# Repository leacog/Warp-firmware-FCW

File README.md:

# LitShow Shield
Mikael Cognell - __mec77__ 

4B25: Coursework Item 5 

St Catharine's College 

_Demo video showing the lightshow in action, notice how the different colours respond to different sounds in the music and not simply volume (this is clearest with the second example)_

## System Overview
The LitShow shield runs on a Freescale/NXP FRDM KL03 evaluation board and  creates a real-time light show to music. The board uses a microphone to measure audio, analyses the signal on the MCU and outputs three channels of Pulse-Width Modulated 12V for LED strips. In the current firmware, the channels each respond to a different frequency band.

## LitShow Shield

#### Microphone
The shield provides two connectors for microphones and expects a 0-3.3V(max) pre-amplied signal with a DC offset at 1/2 VCC (DC offset is adjustable in software). The 3-pin connector matches the pinout of many commonly available electret microphone breakout boards - such as the [adafruit MAX4477](https://www.adafruit.com/product/1063). The 5-pin connector matches the pinout of the adafruit breakoutboard for the [MAX9814](https://www.adafruit.com/product/1713) with Automatic Gain Control.

The output from the microphone is interfaced to the MCU via a RC low-pass filter, with a -3dB frequncy of 20kHz. Furhter work on filtering could be useful, as the microphone still picks up some noise from the serial communication.
#### 12V Output Stage
Three NPN bipolar transistors ([BCP56T1G](https://www.onsemi.com/pdf/datasheet/bcp56t1-d.pdf)) in a common emitter configuration amplify the MCU PWM output. The 12V rail for the LEDs is supplied by an external power supply, connected via a barrel jack at the edge of the shield. MOSFETs would be better suited for this switching application - most enchancment mode NPN mosfets with the required current rating would make good replacements - but these were the only components I had on hand.

#### Hardware files
KiCad PCB project files are included in the repo. Note that they are designed for a single sided board, as I'm etching my PCB at home using a positive photoresist method. If ordering boards from a fab, it's worth considering rerouting the board to be double sided as certain headers (e.g. microphone header) currently have to be soldered on the wrong side and jumper resistors could be replaced by vias.

<p align="center">

</p>

## FRDM-KL03Z Firmware
The shield connects to a Freescale/NXP FRDM KL03 evaluation board, which performs the signal processing of the audio and PWM generation. The software is based on the Warp-firmware, but most of the facilities have been removed and only the serial communication, clock & power management remain. 

The software is split into three components/source files:
#### [ADC.c](src\boot\ksdk1.1.0\ADC.c) - Analog to digtal conversion
The ADC is configured to sample the audio at 38kHz to fulfill the nyquist sampling criteria for the audible range. 
To ensure a constant delay between samples, the ADC operates in continuous conversion mode. 
At the completion of a conversion (i.e. a measurment), an interupt signal is generated and the <code>ADC0_IRQHandler()</code> ISR stores the latest sample in a buffer. 

Using interupts as opposed to e.g. a polling approach allows the main FFT algorithm to run while the next batch of samples are collected.
Also, instead of checking if the buffer is filled inside the interupt routine, the ADC is deactivated (by disconnecting it from its clock source) until the buffer is transfered into the FFT buffer.
This avoids interrupts firing when the buffer is already filled and we are waiting for the previous FFT to finish.

#### [FFT.c](src\boot\ksdk1.1.0\FFT.c) - Fast Fourier Transform
To extract frequency information, a discrete fourier transform is computed on the sample buffer using a costum implementation of a recursive Radix-2 FFT algorithm. The MKL03Z32VFK4 MCU is relatively constrained in memory, with only 2KB of SRAM. To minimize memory usage and increase performance the following design choices were made.

* **The FFT algorithm is implemented in-place** i.e. operates directly on the input array. This means the memory requirements scale as $O(n)$ as opposed to $O(n log(n) )$.

* **The [twiddle factors](https://en.wikipedia.org/wiki/Twiddle\_factor) are precomputed**. This avoids any computation of trigonometric quantities at run-time. Similarly (although much less critical), the bit reversal is also implemented using a look-up table instead of by bit operations. To generate the twiddle factors and bitReverse arrays, the python command line scripts <code> [twiddle_FPA.py](src\boot\ksdk1.1.0\FFT.c)</code> and <code> [bitReverse.py](src\boot\ksdk1.1.0\FFT.c)</code> are provided under <code>/pythonScripts</code>.

* **Divides and multiplications are implemented as shifts**.  As the MCU lacks a Floating Point Unit, the twiddle factors which lie between 1 and -1 are implemented using Fixed Point Arithmetic. A twiddle factor of 1 is represented by 32768 in the FPA arithmatic. After multiplying by the twiddle factors, the result needs to be normalized down again to prevent overflows. This is why 1 is mapped to a power of 2, so that the normalization can be achived by shifting rather than by division. From practical tests, a divide by e.g. 1000 on an <code>int32_t</code> is about 30 times slower than a right shift operation. After many trials using <code>memcpy()</code> to implement fast divisions of signed integers, I found out that the compiler automatically recognizes division by powers of two and implements them as shifts -even with signed numbers where the signbit needs to be considered.

* **Bit Reversal and FFT buffers never co-exist on the stack**. To minimize the peak demand on the stack, the sample re-ordering via bit-reversal which is required at the start of the FFT is executed before the complex array is placed on the stack. This way the two arrays never co-exist on the stack. The maximum demand comes from the complex array, which is $N \times 2 \times$ <code>sizeof(int16_t)</code> of memory on the stack (514 Bytes for 128 point FFT). Still, to accomodate the high memory demand, the default Warp linker script is modified to increase maximum size of the stack, and several modifications to the Warp firmware minimize the RAM usage (which leaves more space for the stack).

The FFT.c file also provides the helper routine <code>octaves()</code> for computing the power spectrum of the FFT and splitting it into octaves. An octave bin covers twice the width in frequency of the one below one - e.g. the 2 lowest FFT bins go in the lowest octave, the 4 next bins in the second octave, the 8 next go in the third octave etc. This is better aligned with the human logarithmic perception of frequency. These octaves are used by the PWM routines to determine brightness values.

#### [PWM.c](src\boot\ksdk1.1.0\PWM.c) - Mapping frequency information to duty cycles
The PWM.c functionality sets up the Timer modules of the MCU to output PWM signals on <code>PTA5</code>, <code>PTA6</code> and <code>PTB6</code>. It contains a function to update the duty cycles for each of the channels, which accepts as arguments a <code>pwmColour</code>struct which maps the respective colour to the corresponding timer instances and channels.

Each time an FFT completes in the main loop, the power spectrum is divided into three bins using the octaves function. The value of each bin then sets the duty cycle of a corresponding colour of LED. This means one LED channel responds to base tones, one to mid-range and one to trebble. There is a lot of scope for increasing the sophistication of the mapping from DFT to brightness values, as the current firmware basically only implements a low-pass, band-pass and high-pass filter (which could be done with 4 capacitors and 4 resistors...).

It also contains some functions to perform further processing of the frequency signals. For the base note, a first-order lag is applied to make the brightness linger more, as this produces a nice effect. 

#### printFFT - rudamentary spectrum analyzer ####
In [boot.c](src\boot\ksdk1.1.0\boot.c), the printFFT function can be uncommented to display power spectrum on a serial terminal connected to the FRDM-KL03Z. This works as a rudamentary spectrum analyzer, to partly validate the functioning of the FFT but also to characterize the response of the microphone of a reference sound source is available.

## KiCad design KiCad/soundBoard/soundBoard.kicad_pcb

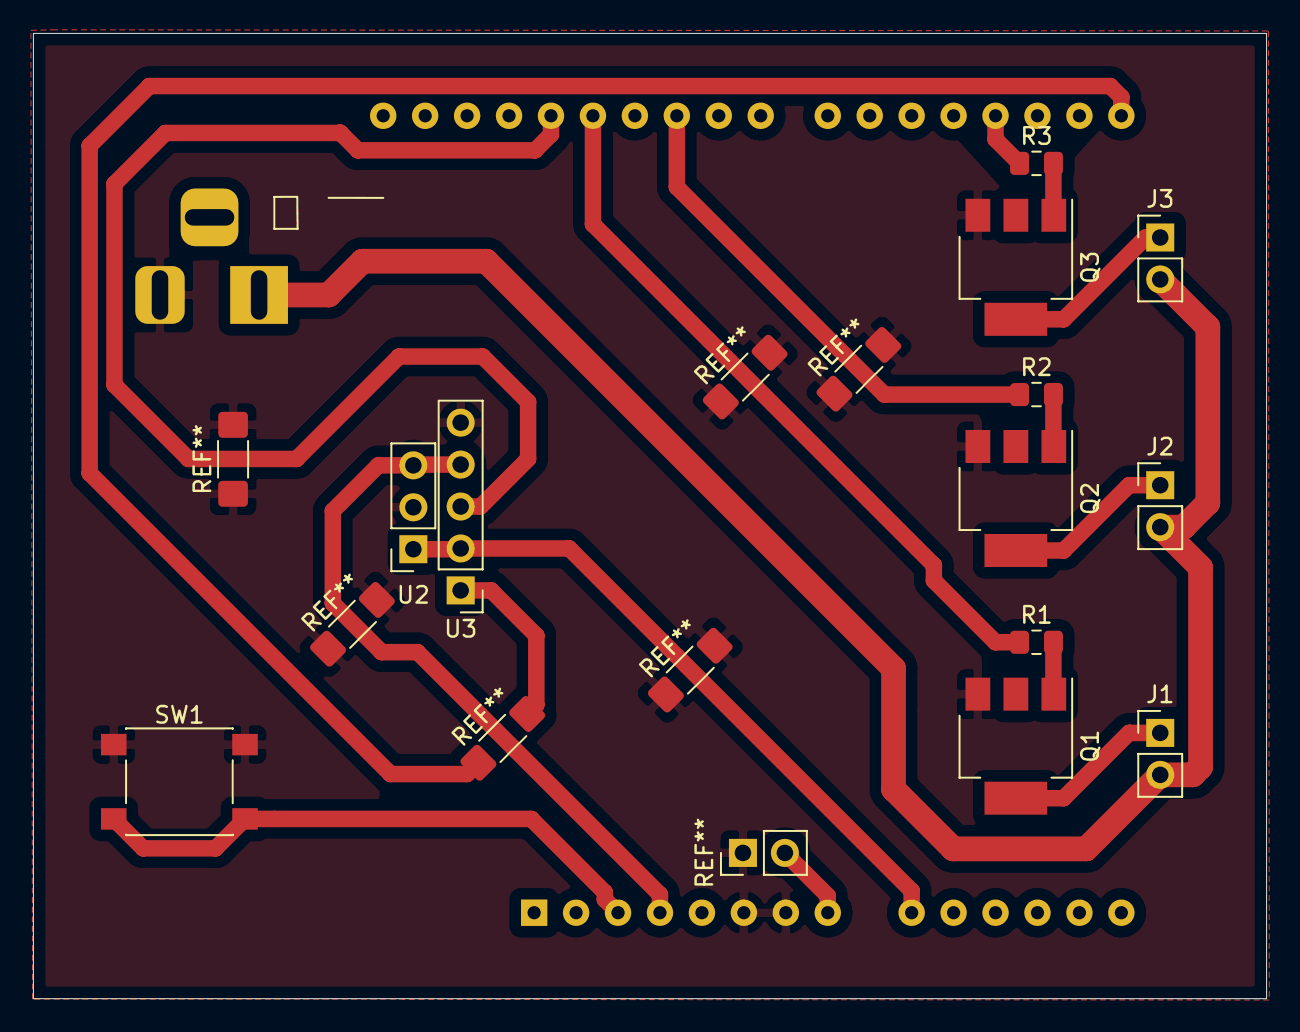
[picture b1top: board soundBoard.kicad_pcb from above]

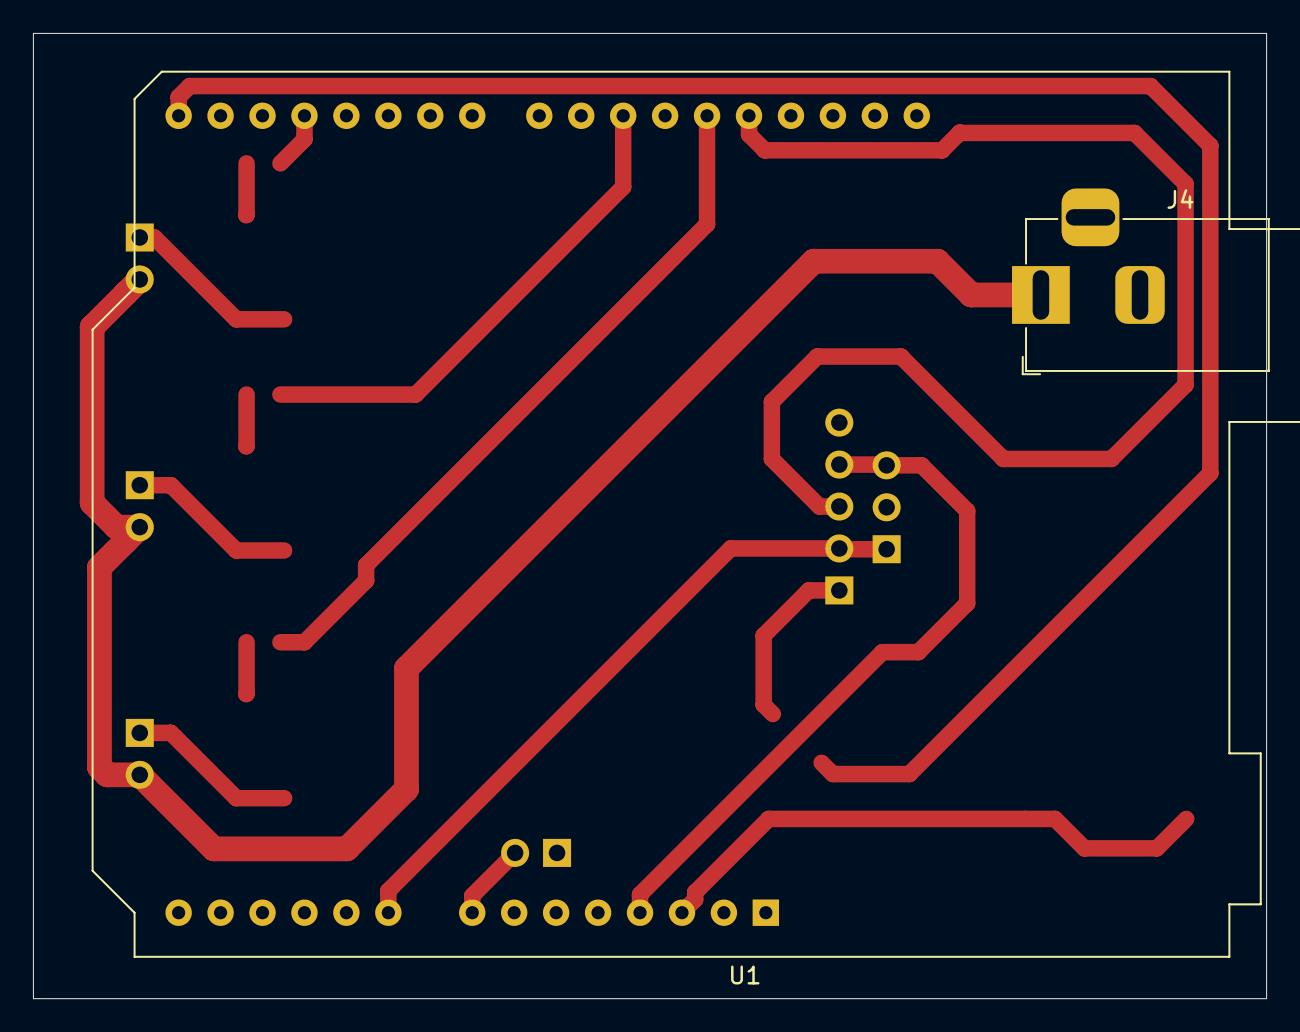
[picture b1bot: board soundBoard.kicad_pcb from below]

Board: 2 copper layers, 74.7 x 58.5 mm, 14 parts (2 on the bottom side), 16 nets.

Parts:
J1: RED; PinHeader_1x02_P2.54mm_Vertical
J2: BLUE; PinHeader_1x02_P2.54mm_Vertical
J3: GREEN; PinHeader_1x02_P2.54mm_Vertical
J4: 12_Barrel_Jack; BarrelJack_Horizontal
Q1, Q2, Q3: BCP56; SOT-223-3_TabPin2
R1, R2, R3: 670; R_0805_2012Metric_Pad1.15x1.40mm_HandSolder
SW1: SW_Push; SW_Push_1P1T_NO_6x6mm_H9.5mm
U1: FRDM-KL03Z; Arduino_UNO_R3
U2: AG_ElectretMic; PinSocket_1x03_P2.54mm_Vertical
U3: RealAG_ElectretMic; PinHeader_1x05_P2.54mm_Vertical

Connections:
+12V: J1.2, J2.2, J3.2, J4.1
/ADC_IN: U1.9, U2.1, U3.2
/AR_ADJUST: U1.15, U3.1
/BLUE_PWM: R3.1, U1.18
/GREEN_PWM: R2.1, U1.25
/RED_PWM: R1.1, U1.27
GND: J4.2, Q1.3, Q2.3, Q3.3, SW1.1, U1.6, U1.7, U1.29, U2.2, U3.5
unnamed: J1.1, Q1.2
unnamed: J2.1, Q2.2
unnamed: J3.1, Q3.2
unnamed: Q1.1, R1.2
unnamed: Q2.1, R2.2
unnamed: Q3.1, R3.2
unnamed: SW1.2, U1.3
unnamed: U1.28, U3.3
VCC: U1.4, U2.3, U3.4

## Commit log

2022-01-06 fixed typo
2022-01-06 Added blocking poll read
2022-01-06 Added adc averaging and bclk/2
2022-01-06 code to test delay
2022-01-06 Added IRS for adc
2022-01-06 moved adc IRQ to boot
2022-01-06 High speed sampling now working
2022-01-06 initial FFT commit
2022-01-06 fixes to FFT and test
2022-01-07 Added complex numbers
2022-01-07 fixes to FFT
2022-01-07 added fft4
2022-01-07 working 16point FFT
2022-01-07 recursive FFT
2022-01-07 start low memory recursive FFT
2022-01-07 trying to fix recursive FFT
2022-01-07 recursive working 32 wide
2022-01-07 big purge
2022-01-07 working purge
2022-01-07 FFT working
2022-01-07 Initial PWM test
2022-01-08 PWM 3 channel working
2022-01-08 inital integration
2022-01-08 rev1 integration
2022-01-09 blinking working for effect is poor
2022-01-09 added octaves and changed RGB function
2022-01-10 Final changes before hardware build
2022-01-11 Started README.md
2022-01-11 Added images folder
2022-01-11 first draft Readme
2022-01-11 split trebble and base
2022-01-11 PWM cleanup and removed some unused
2022-01-12 added python scripts to repo
2022-01-25 Holiday last changes
2022-01-25 implemented simultainous sampling and proccessing
2022-01-25 fixes to simultanoues mods
2022-01-25 Fixed point arithmetic for FFT
2022-01-25 compile bugs fixes to FFT FPA
2022-01-26 Fixes to simultaneous ADC and FFT
2022-01-27 all components working
2022-01-28 128 point FFT implemented
2022-01-28 Finished README and added images
2022-01-28 Added KiCad Hardware Files
2022-01-28 fixed schematic image
2022-01-28 fixed caps .JPG bug
2022-01-28 relative path for schematic PDF
